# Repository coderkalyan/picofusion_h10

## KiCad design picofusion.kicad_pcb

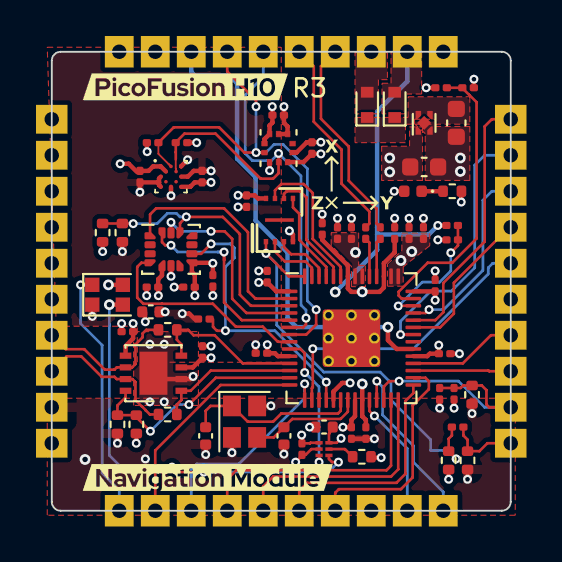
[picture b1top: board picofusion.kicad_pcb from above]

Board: 4 copper layers, 25.5 x 25.5 mm, 70 parts (1 on the bottom side), 55 nets.

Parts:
C1, C2, C4, C6, C7, C9, C10, C11, C13, C15, C18, C22, C23, C24, C26, C27, C28, C29, C32, C33: 0u1; C_0201_0603Metric
C3, C25: 1u; C_0201_0603Metric
C5, C8: 10p; C_0402_1005Metric
C14, C16: 0u1; C_0603_1608Metric
C17: 2u2; C_0201_0603Metric
C19: 10n; C_0201_0603Metric
C30: 0u1; C_0402_1005Metric
C31: 1u; C_0402_1005Metric
D1: 1PS79SB30; D_SOD-523
D2: GREEN; LED_0402_1005Metric
D3: BZX58550-B5V6; D_SOD-523
D4: WS2812B-2020
J1: NORTH; PinCastellation_1x10_P2.00mm_Vertical
J2: EAST; PinCastellation_1x10_P2.00mm_Vertical
J3: WEST; PinCastellation_1x10_P2.00mm_Vertical
J4: SOUTH; PinCastellation_1x10_P2.00mm_Vertical
R1, R24: 10K; R_0201_0603Metric
R2, R3: 27; R_0201_0603Metric
R6: 1K5; R_0402_1005Metric
R7, R14, R21, R23: 10K; R_0402_1005Metric
R8, R9: 1K5; R_0201_0603Metric
R10, R11: 100K; R_0402_1005Metric
R12, R13, R18, R19: 0; R_0402_1005Metric
R15, R16, R17, R22: 22K; R_0201_0603Metric
R20: 1K; R_0201_0603Metric
TP1: TestPoint; TestPoint_Pad_1.0x1.0mm
U1: W25Q16; 8-USON
U2: RP2040; RP2040-QFN-56
U3: TLV71333PDQN; Texas_X2SON-4_1x1mm_P0.65mm
U4: ICM-42688-P; LGA-14_3x2.5mm_P0.5mm_LayoutBorder3x4y
U5: BMM150; WLCSP-12_1.56x1.56mm_P0.4mm
U6: ICP20100; PQFN50P200X200X85-10N
U7: TJA1051TK-3; DFN-8-1EP_3x3mm_P0.65mm_EP1.55x2.4mm
U8: 74LVC1T45GS; PSON35P100X100X35-6N
Y1: 12MHz; Crystal_SMD_2520-4Pin_2.5x2.0mm

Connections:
+1V1: C1.1, C2.1, C3.1, U2.23 (DVDD), U2.45 (VREG_VOUT), U2.50 (DVDD)
+3V3: C4.1, C6.1, C7.1, C9.1, C10.1, C13.1, C15.1, C16.1, C17.2, C18.2, C19.1, C22.2, C23.1, C24.1, C25.1, C26.1, C27.1, C29.2, C32.2, C33.1, D2.2 (A), J3.10, R1.1, R8.1, R9.1, R11.1, R14.1, R15.1, R21.1, R23.1, U1.8 (VCC), U2.1 (IOVDD), U2.10 (IOVDD), U2.22 (IOVDD), U2.33 (IOVDD), U2.42 (IOVDD), U2.43 (ADC_AVDD), U2.44 (VREG_IN), U2.48 (USB_VDD), U2.49 (IOVDD), U3.1 (OUT), U4.5 (VDDIO), U4.8 (VDD), U5.A1 (PS), U5.B2 (VDDIO), U5.E5 (VDD), U6.1 (CSB), U6.5 (VDD), U6.10 (VDDIO), U7.5 (VIO), U8.1 (VCCA)
+5V: C28.1, C30.2, C31.1, D1.2 (A), D4.4 (VDD), J1.9, J3.6, R17.1, U7.3 (VCC), U8.6 (VCCB)
/3V3_SENSE: R15.2, R16.1, U2.41 (GPIO29_ADC3)
/5V_SENSE: R17.2, R22.1, U2.40 (GPIO28_ADC2)
/BOOTSEL: J2.10, R19.1, R20.1
/BUZZER: J4.3, U2.15 (GPIO12)
/CAN_N: J3.7, R13.2, U7.6 (CANL)
/CAN_P: J3.8, R12.2, U7.7 (CANH)
/CAN_SILENT: R10.1, R11.2, U2.13 (GPIO10), U7.8 (S)
/DRDY_ICM42688P: U2.8 (GPIO6), U4.4 (INT)
/I2C0_SCL: J1.4, R8.2, U2.7 (GPIO5), U5.A3 (SCK), U6.2 (SCL/SCLK)
/I2C0_SDA: J1.5, R9.2, U2.6 (GPIO4), U5.B4 (SDI), U6.4 (SDA/SDI)
/IMU_HEATER: J4.2, U2.14 (GPIO11)
/LED: D4.1 (DOUT), J4.1
/NEOPIXEL_3V3: U2.9 (GPIO7), U8.3 (A)
/PIO0_CAN_RX: R13.1, U2.11 (GPIO8), U7.4 (RXD)
/PIO0_CAN_TX: R12.1, U2.12 (GPIO9), U7.1 (TXD)
/PWM7B_FSYNC: R24.1, U2.18 (GPIO15), U4.9 (FSYNC)
/QSPI_SCK: U1.6 (CLK), U2.52 (QSPI_SCLK)
/QSPI_SD0: U1.5 (DI(IO0)), U2.53 (QSPI_SD0)
/QSPI_SD1: U1.2 (DO(IO1)), U2.55 (QSPI_SD1)
/QSPI_SD2: U1.3 (IO2), U2.54 (QSPI_SD2)
/QSPI_SD3: U1.7 (IO3), U2.51 (QSPI_SD3)
/QSPI_nCS: R20.2, R21.2, TP1.1, U1.1 (~CS), U2.56 (QSPI_SS)
/RESV1: J2.5, U2.16 (GPIO13)
/RUN: C11.1, J2.9, R1.2, R18.1, U2.26 (RUN)
/SPI0_MISO: U2.2 (GPIO0), U4.1 (AD0/SDO)
/SPI0_MOSI: U2.5 (GPIO3), U4.14 (SDA/SDI)
/SPI0_SCK: U2.4 (GPIO2), U4.13 (SCL/SCLK)
/SPI0_nCS: R7.1, R23.2, U2.3 (GPIO1), U4.12 (nCS)
/SPI1_MISO: J2.2, U2.36 (GPIO24)
/SPI1_MOSI: J2.3, U2.39 (GPIO27_ADC1)
/SPI1_SCK: J2.1, U2.38 (GPIO26_ADC0)
/SPI1_nCS: J2.4, U2.37 (GPIO25)
/SWCLK: J4.9, U2.24 (SWCLK)
/SWDIO: J4.10, U2.25 (SWD)
/UART0_CTS_TELEM: J4.6, U2.29 (GPIO18)
/UART0_RTS_TELEM: J4.7, U2.30 (GPIO19)
/UART0_RX_TELEM: J4.5, U2.28 (GPIO17)
/UART0_TX_TELEM: J4.4, U2.27 (GPIO16)
/UART1_RX_GNSS: J2.7, U2.32 (GPIO21)
/UART1_TX_GNSS: J2.8, U2.31 (GPIO20)
/USB_DN: J1.7, R3.2
/USB_DP: J1.6, R2.2
/USB_MCU_DN: R3.1, U2.46 (USB_DM)
/USB_MCU_DP: R2.1, U2.47 (USB_DP)
/USB_VBUS: J1.3, U2.34 (GPIO22)
/XIN: C5.1, U2.20 (XIN), Y1.1
/XOUT: C8.1, U2.21 (XOUT), Y1.3
GND: C1.2, C2.2, C3.2, C4.2, C5.2, C6.2, C7.2, C8.2, C9.2, C10.2, C11.2, C13.2, C14.2, C15.2, C16.2, C17.1, C18.1, C19.2, C22.1, C23.2, C24.2, C25.2, C26.2, C27.2, C28.2, C29.1, C30.1, C31.2, C32.1, C33.2, D3.2 (A), D4.2 (VSS), J1.8, J1.10, J2.6, J3.9, J4.8, R6.2, R7.2, R10.2, R16.2, R18.2, R19.2, R22.2, R24.2, U1.4 (GND), U2.19 (TESTEN), U2.57 (GND), U3.2 (GND), U3.5 (GND), U4.6 (GND), U5.A5 (CSB), U5.C1 (SDO), U5.C5 (GND), U5.E1 (GND), U5.E3 (GND), U6.3 (VSS), U6.6 (AD0/SDO), U6.8 (RESV), U6.9 (RESV), U7.2 (GND), U7.9 (GND), U8.2 (GND), Y1.2, Y1.4
unnamed: C14.1, D1.1 (K), D3.1 (K), U3.3 (EN), U3.4 (IN)
unnamed: D2.1 (K), R6.1
unnamed: D4.3 (DIN), U8.4 (B)
unnamed: R14.2, U8.5 (DIR)

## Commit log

2022-04-28 finish schematic draft
2022-07-07 schematic: update regulator, sensors
    * simplify some sensor schematics
    * replace 3v3 regulator
    * DRC and footprints
2022-07-07 draft layout improvements
2022-07-10 backup before moving to 0201
2022-07-19 a little more work
2022-07-19 layout: first draft at 19x19
2022-07-19 add reverse/overvoltage protection
2022-07-19 schematic: add one more decoupling cap for rp2040
2022-07-20 schematic/pcb: more routing, add another decoupling cap
2022-07-20 update libs
2022-07-23 Add new CAN transceiver and castellated holes
2022-07-23 Fix duplicate pin headers
2022-07-23 layout: update castellations, pinout, reorder
2022-07-23 schematic: update power protection diode wiring
2022-07-23 layout: update 3d models
2022-08-05 Add traces to various components
2022-08-06 routing cleanup, merge minor schematic fixes
2022-08-13 Replace current transceiver with TJA1051TK/3118 and add work on GND/power routing
2022-08-14 layout: cleanup, planes, some drc
2022-08-20 Finish R01A
2022-08-21 Finish R01B
2022-09-05 more work
2022-09-17 finish R02B
2022-10-22 R02B: more work
2022-10-22 R02B: finish new discussion modifications
2022-10-24 remove unused bl9161 symbol
2022-10-24 more board cleanup, silkscreen draft
2022-10-24 update footprints, fix drc
2022-10-25 update gitignore
2022-10-25 h10: add graphics, fix drc, minor modifications
2022-12-01 h10: r2 final
2023-01-22 added f412 and did test routing
2023-01-23 schematic: reformat and R3 release candidate
    * reformat schematic
    * minor fixes from R2 testing
    * no functionality differences
2023-01-31 update standard libs
2023-11-01 schematic: more improvements towards R3
2025-03-31 schematic: refresh sensors, mcu and redo pinout
    * update rp2040 -> rp2350b
    * update icm-42688p -> icm-45686
    * update bmm150 -> bmm350
    * add current sensing logic
    * change pinout count and update pinout
    * drop led and heater support
2025-03-31 schematic: cleanup
2025-03-31 schematic: footprint assignment
